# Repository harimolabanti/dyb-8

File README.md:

# dyb-8
8 key choc macro pad with onboard RP2040 controller

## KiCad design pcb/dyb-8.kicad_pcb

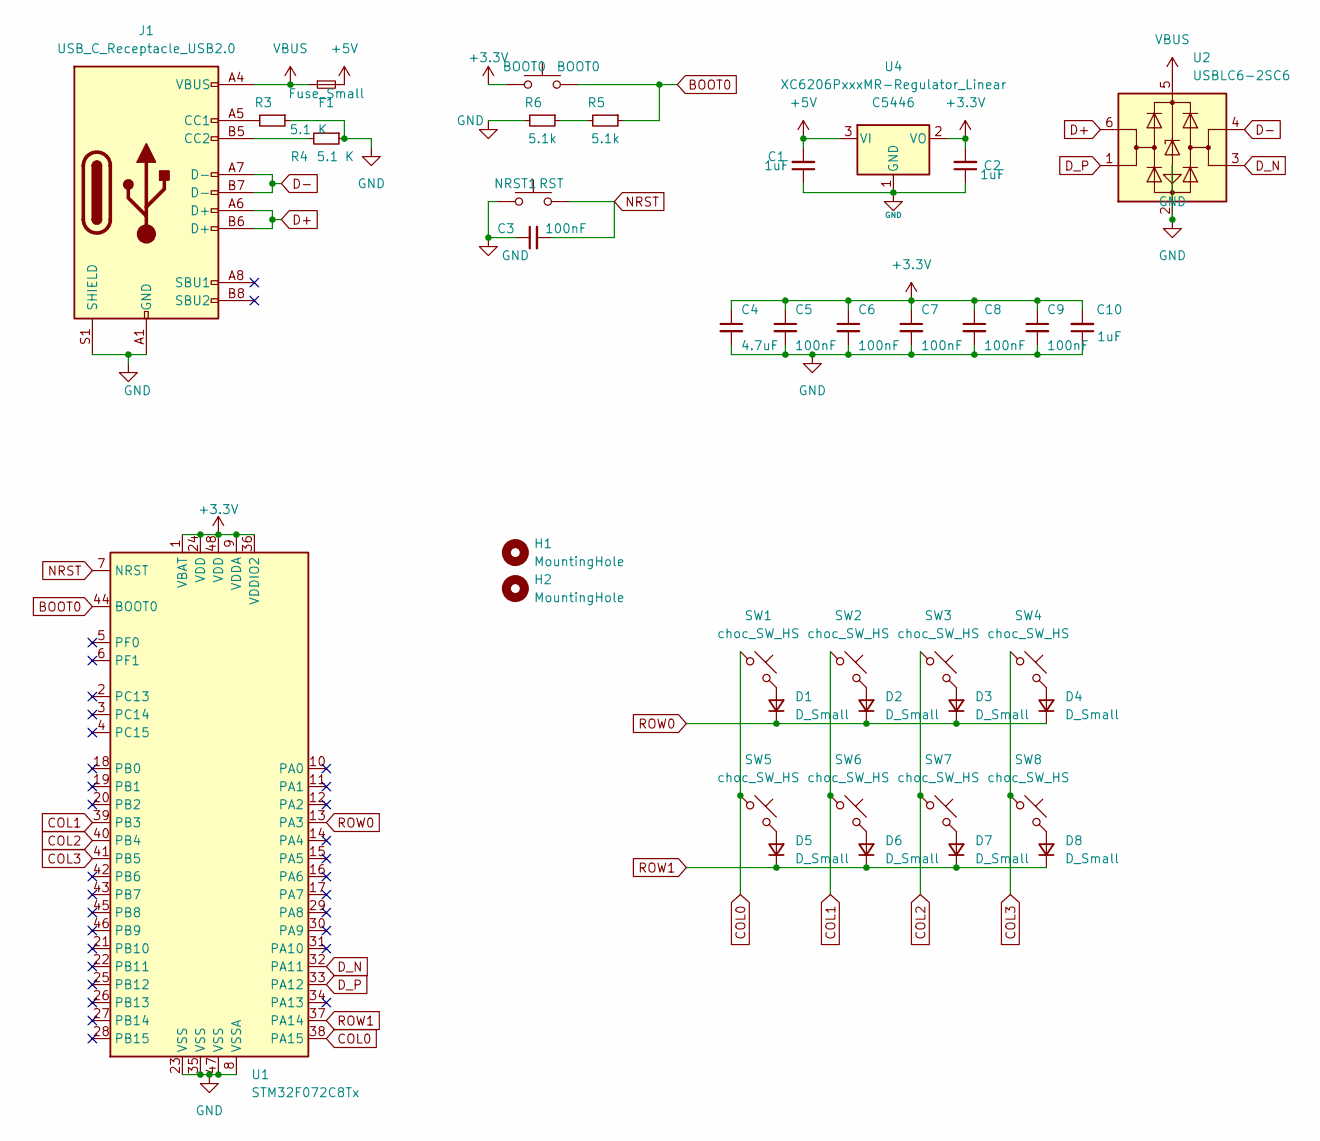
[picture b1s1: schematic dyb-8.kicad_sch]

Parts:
BOOT0: BOOT0; SW_SPST_SKQG_WithoutStem
C1, C2, C10: 1uF; C_0402_1005Metric; LCSC C52923
C3, C5, C6, C7, C8, C9: 100nF; C_0402_1005Metric; LCSC C307331
C4: 4.7uF; C_0402_1005Metric; LCSC C52923
D1, D2, D3, D4, D5, D6, D7, D8: D_Small; D_SOD-123
F1: Fuse_Small; Fuse_1206_3216Metric
H1, H2: MountingHole; MountingHole_2.2mm_M2
J1: USB_C_Receptacle_USB2.0; USB_C_Receptacle_HRO_TYPE-C-31-M-12
NRST1: RST; SW_SPST_SKQG_WithoutStem
R3, R4: 5.1 K; R_0402_1005Metric
R5, R6: 5.1k; R_0402_1005Metric
SW1, SW2, SW3, SW4, SW5, SW6, SW7, SW8: choc_SW_HS; SW_choc_v1_HS_1u_18_17
U1: STM32F072C8Tx; LQFP-48_7x7mm_P0.5mm
U2: USBLC6-2SC6; SOT-23-6
U4: XC6206PxxxMR-Regulator_Linear; SOT-23; LCSC C5446

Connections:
+3.3V: BOOT0.1, C2.2, C4.1, C5.1, C6.1, C7.1, C8.1, C9.1, C10.2, U1.1 (VBAT), U1.9 (VDDA), U1.24 (VDD), U1.36 (VDDIO2), U1.48 (VDD), U4.2 (VO)
+5V: C1.2, F1.2, U4.3 (VI)
BOOT0: BOOT0.2, R5.1, U1.44 (BOOT0)
COL0: SW1.1, SW5.1, U1.38 (PA15)
COL1: SW2.1, SW6.1, U1.39 (PB3)
COL2: SW3.1, SW7.1, U1.40 (PB4)
COL3: SW4.1, SW8.1, U1.41 (PB5)
D+: J1.A6 (D+), J1.B6 (D+), U2.6 (I/O1)
D-: J1.A7 (D-), J1.B7 (D-), U2.4 (I/O2)
D_N: U1.32 (PA11), U2.3 (I/O2)
D_P: U1.33 (PA12), U2.1 (I/O1)
GND: C1.1, C2.1, C3.1, C4.2, C5.2, C6.2, C7.2, C8.2, C9.2, C10.1, J1.A1 (GND), J1.A12 (GND), J1.B1 (GND), J1.B12 (GND), J1.S1 (SHIELD), NRST1.1, R3.1, R4.1, R6.2, U1.8 (VSSA), U1.23 (VSS), U1.35 (VSS), U1.47 (VSS), U2.2 (GND), U4.1 (GND)
NRST: C3.2, NRST1.2, U1.7 (NRST)
unnamed: D1.2 (A), SW1.2
unnamed: D2.2 (A), SW2.2
unnamed: D3.2 (A), SW3.2
unnamed: D4.2 (A), SW4.2
unnamed: D5.2 (A), SW5.2
unnamed: D6.2 (A), SW6.2
unnamed: D7.2 (A), SW7.2
unnamed: D8.2 (A), SW8.2
unnamed: J1.A5 (CC1), R3.2
unnamed: J1.B5 (CC2), R4.2
unnamed: R5.2, R6.1
ROW0: D1.1 (K), D2.1 (K), D3.1 (K), D4.1 (K), U1.13 (PA3)
ROW1: D5.1 (K), D6.1 (K), D7.1 (K), D8.1 (K), U1.37 (PA14)
VBUS: F1.1, J1.A4 (VBUS), J1.A9 (VBUS), J1.B4 (VBUS), J1.B9 (VBUS), U2.5 (VBUS)

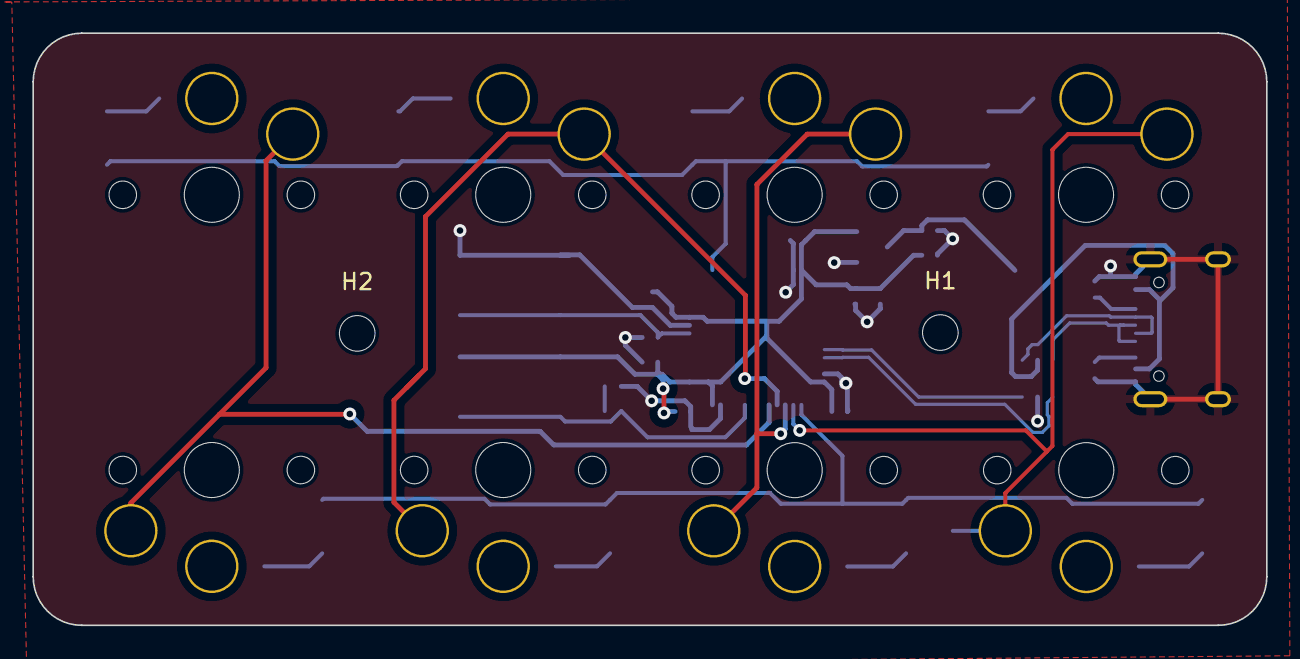
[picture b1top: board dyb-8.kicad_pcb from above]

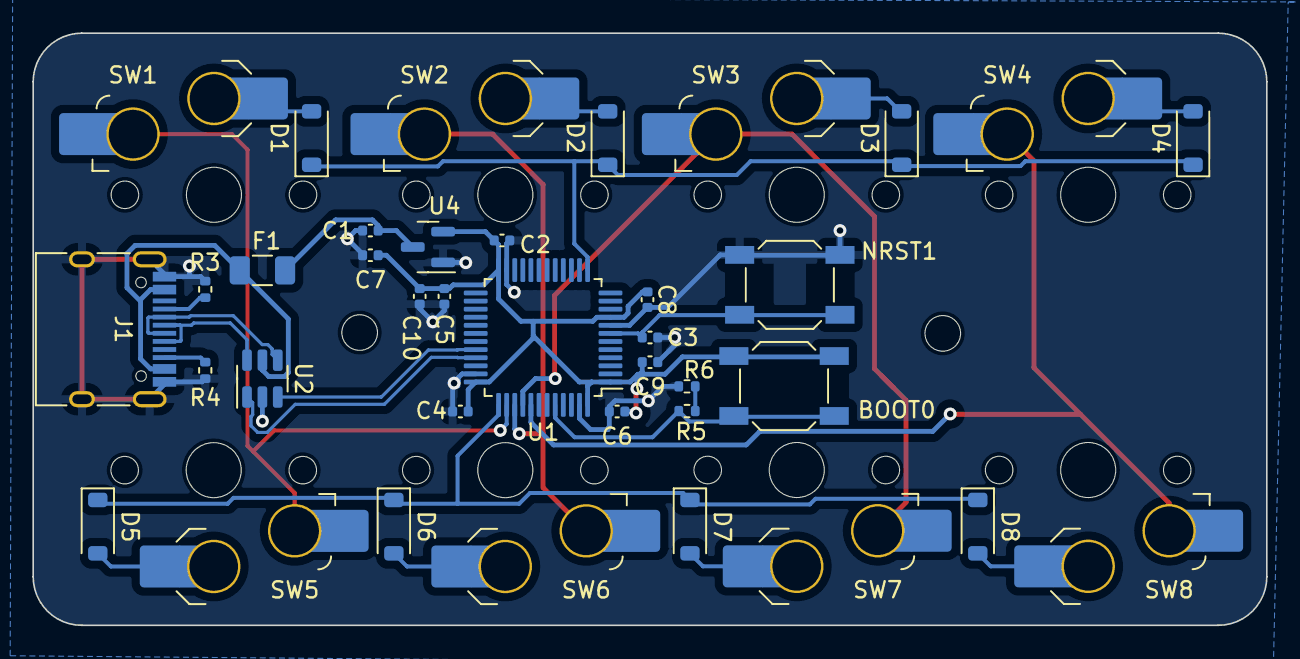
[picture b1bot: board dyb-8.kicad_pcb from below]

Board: 2 copper layers, 76.2 x 36.6 mm, 39 parts (37 on the bottom side), 27 nets.

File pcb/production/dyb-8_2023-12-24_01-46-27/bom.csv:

Designator,Footprint,Quantity,Value,LCSC Part #
BOOT0,SW_SPST_SKQG_WithoutStem,1,BOOT0,
"C1, C10, C2",0402,3,1uF,C52923
"C3, C5, C6, C7, C8, C9",0402,6,100nF,C307331
C4,0402,1,4.7uF,C52923
"D1, D2, D3, D4, D5, D6, D7, D8",D_SOD-123,8,D_Small,
F1,1206,1,Fuse_Small,
"H1, H2",MountingHole_2.2mm_M2,2,MountingHole,
J1,USB_C_Receptacle_HRO_TYPE-C-31-M-12,1,USB_C_Receptacle_USB2.0,
NRST1,SW_SPST_SKQG_WithoutStem,1,RST,
"R3, R4",0402,2,5.1 K,
"R5, R6",0402,2,5.1k,
"SW1, SW2, SW3, SW4, SW5, SW6, SW7, SW8",SW_choc_v1_HS_1u_18_17,8,choc_SW_HS,
U1,LQFP-48_7x7mm_P0.5mm,1,STM32F072C8Tx,
U2,SOT-23-6,1,USBLC6-2SC6,
U4,SOT-23,1,XC6206PxxxMR-Regulator_Linear,C5446

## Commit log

2023-12-23 routing and schematic complete
